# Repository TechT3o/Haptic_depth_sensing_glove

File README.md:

# Haptic_depth_sensing_glove

Haptic feedback glove device that uses a motor camera and mini motor disks to help visually impaired people understand the 3d space around them.

The idea is to mount a small camera on the palm of the visually impaired user, construct the depth map, and perform sensory substitution of vision by using a high-resolution haptic feedback glove comprised of an array of vibrational mini DC motor disks to assign a different intensity in the direction where the user's hand is pointing at, analogous to how close the object is.

The goal is for the user to be able to identify what type of object their hand is pointing at for object recognition and object fetching and for the user to be able to do wayfinding and navigate in a room using the device.

User studies that examine the usability (Learnability, Efficiency, Memorability, Errors, Satisfaction) and effectiveness of the device will be done.

# Hardware

- 1x [ESP32](https://www.espressif.com/en/products/socs/esp32)
- 1x [OV5640 camera module](https://www.amazon.com/Cameras-2592X1944-Industrial-Windows-Raspberry/dp/B088RD74VC?th=1)
- 20x [Mini motor disk](https://www.adafruit.com/product/1201#technical-details)
- 20x [p2n222A npn transistor](https://www.onsemi.com/pdf/datasheet/p2n2222a-d.pdf)
- 20x 30 Ohms resistor
- 20x 2.2k Ohms resistor
- 20x 33 pF capacitor
- 20x 1N4001 diode
- 20x [motor circuit PCB](https://github.com/TechT3o/Haptic_depth_sensing_glove/tree/main/PCB%20files)

## Motor driver circuit

The mini disk motors require around 100 mA of current in order to rotate at full speed with 5V power. The Arduino output pins can provide up to 10 mA, therefore we need a driver circuit to be able to power the motor using a PWM signal. The circuit shown in Figure 1 was built. It uses an NPN transistor whose base is connected to the GPIO output pin of the Arduino. When the PWM signal gets applied to the base of the transistor the Collector Emitter channel opens and current from the VCC flows through the disk motor and makes it spin with intensity analogous to the PWM signal. The resistor R2 limits the current flowing through the disk motor. A value of 30 Ohms was selected as 5V/30 = 166 mA max current that could flow through R2 ignoring rest of the circuit resistances. R1 was selected to limit the base current. As the base current is very small values of up to 5k could be selected but the chosen value for R1 in this project was 2.2k Ohms. The capacitor is used to soften voltage spikes from the power supply and suppress electrical noise from the motor's rotation and a diode is put to protect against back EMF.

*Figure 1: Motor driver circuit*

The PCB of this circuit shown in Figure 2 was made and the Gerber files were sent to [OSHPARK](https://oshpark.com/) for manufacturing.

*Figure 2: Motor driver PCB*

The received PCBs arrived and the components were soldered on top of it with the disk motors attached to the back of the PCB.

*Figure 3: PCB*

*Figure 4: Soldered circuits and motor coordinates*

## Camera

When choosing the camera we wanted a camera with a small size that could fit the device, as little distortion as possible (no wide angle cameras that tend to have a lot of barrel distortion), low latency and good enough resolution for the depth estimation model to give accurate results. The camera selected was a 5MP USB Camera Webcam with 60 Degree FOV and Autofocus Lens by IFWATER.

It used the OV5640 CMOS (Complementary Metal-Oxide-Semiconductor) image sensor which has high resolution of 2592 x 1944 pixels and can achieve frame rates of 30 FPS.

The location of the camera was another dilemma in our design consideration. As originally intended, it was supposed to be connected to the user's body. However, by relocating the camera to the palm, we eliminated the need to determine the depth relative to the hand, thereby simplifying the entire system. Placing the camera on the palm allows for a more natural interaction with the environment.

## Microcontroller
The microcontroller picked is an ESP32 DevkitC module. It was selected because it is affordable, has the options of wireless connectivity and low power consumption and unlike the Arduino Nano 33 BLE Sense which was the first attempt has no upper limit into how many GPIO pins can provide a PWM signal concurrently. 

*Figure 5: ESP32 module*

## Depth Estimation

In order to estimate the depth from a mono camera the vision transformer model DPT-Large by Intel was used. This transformer was trained on 1.4 million images for monocular depth estimation and it can predict the relative depth in an image frame. The Python class [MonoDepthEstimator](https://github.com/TechT3o/Haptic_depth_sensing_glove/blob/main/depth_estimation.py) implements this transformer with functions that can find the depth of a frame. For sanity checking the depth frames are visualized as a 3D point cloud using the [3D reconstruction](https://github.com/TechT3o/Haptic_depth_sensing_glove/blob/main/3d_reconstruct.py) script and the relative distances between the objects captured seem reasonable and is accurate for which object is closer to the camera. A sample depth video that is used to test the glove in its early stages and to visualize the depth estimation created by the [depth video creating script](https://github.com/TechT3o/Haptic_depth_sensing_glove/blob/main/depth_video_creating_script.py) is shown in Figure 5.

*Figure 6: Mono depth video example*

*Figure 7: Point cloud*

## Intensity mapping

The [IntensityMapper](https://github.com/TechT3o/Haptic_depth_sensing_glove/blob/main/intensity_mapper.py) class is responsible for getting the depth map and the positions of the motors on the glove and getting the PWM values by averaging the values around the corresponding pixel in the depth map. It performs the mapping by being input teh positions of the motors in a coordinate system on the frame of the device.

## Serial Communication

The [serial communicator](https://github.com/TechT3o/Haptic_depth_sensing_glove/blob/main/serial_com.py) class is responnsible for connecting the Python backend serially to the ESP32, transmitting the motor intensities and validating if those intensities were properly received.

## Microcontroller script

The [ESP32 script](https://github.com/TechT3o/Haptic_depth_sensing_glove/blob/main/motor_test.ino) is responsible for listening to the serial communication channel and reading and decoding the comma seperated string message that has the motor itnensities sent by the Python backend. Then it assigns these PWM intensities as PWM signals to the pins corresponding to each motor and send back the received intensities for the backend to confirm whether the communication was correct.

 ## Helper scripts

The [camera calibration](https://github.com/TechT3o/Haptic_depth_sensing_glove/blob/main/calibrate_cam_script.py) script is used to obtain camera parameters such as the foundational matrix, the intrinsic and extrinsic parameters and the lens distortions to be used in the 3D reconstruction or in estimating the depth.

## Prototype

A generic hand shaped frame was formed by gluing together wooden popsickles. Then all the electronics were mounted on top of the frame. The camera and the ESP32 are connected to the laptop through USB ports. The cables controlling the motors are connected to respective digital and analog pins (they both can provide PWM signals) of the ESP32. Lastly the power supply wires are connected to a 5V pwoer supply output and the ground of the power supply and the ESP32 are connected.

By running the [main.py](https://github.com/TechT3o/Haptic_depth_sensing_glove/blob/main/main.py) script we can operate the prototype and a visualziation that shows what the device captures and where the intensity of each motor is found from is shown.

*Figure 6: Prototype*

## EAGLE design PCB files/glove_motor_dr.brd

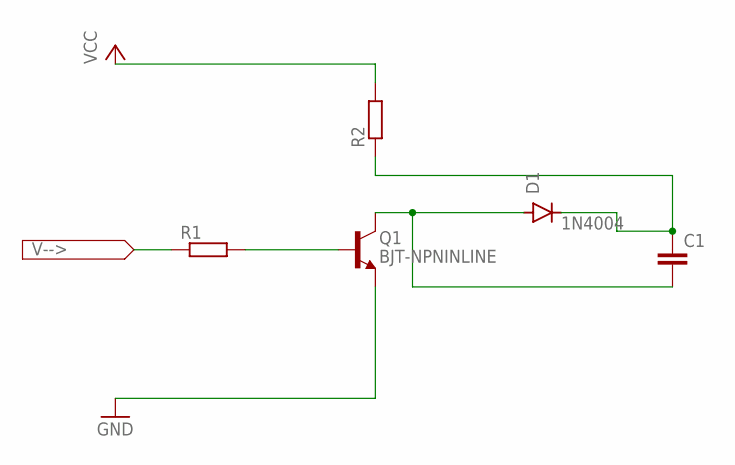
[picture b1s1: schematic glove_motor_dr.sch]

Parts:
C1: C-EU025-024X044; C025-024X044
D1: 1N4004; DO41-10
Q1: BJT-NPNINLINE; TO92I
R1, R2: R-EU_0207/7; 0207/7

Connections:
GND: Q1.E
MOTOR: C1.2, D1.A, Q1.C
unnamed: C1.1, D1.C, R2.1
unnamed: Q1.B, R1.2
VCC: R2.2

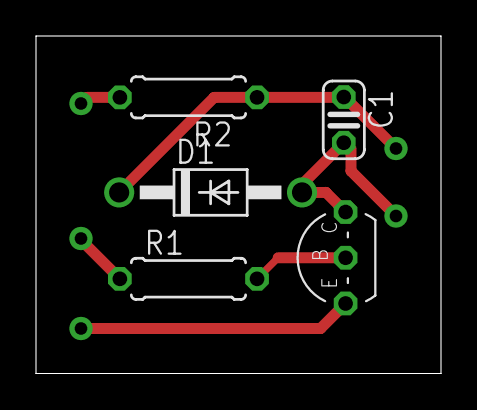
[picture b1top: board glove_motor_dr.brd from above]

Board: 2 copper layers, 22.5 x 18.8 mm, 5 parts (0 on the bottom side), 3 nets.

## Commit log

2023-10-16 Initial commit! Added depth_estimation.py a script that uses a depth transformer to find the depth of the images captured by laptops' camera Added calibrate_cam_script.py which can either use a folde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
2023-10-17 Refactored code
2023-11-07 added close camera to depth_estimation.py Created depth_video_creating_script.py Created intensity_mapper.py Created serial_com.py Created main.py
2023-11-07 Course deliverables
    Added course deliverable templates
2023-11-07 Update index.md
    Added basic information to index.md
2023-11-07 Update proposal.md
    Started completing proposal.md
2023-11-08 Update proposal.md
    Completed some more of proposal.md
2023-11-08 Update proposal.md
    Further updated proposal.md
2023-11-08 Update README.md
    Updated readme with hardware requirements and motor driver circuit details
2023-11-08 Update README.md
    Added text information for mono depth estimation
2023-11-08 Added Arduino code
2023-11-08 PCB files
    Added schematic, board file as well as the cam files used to manufacture the PCBs of the motor drivers
2023-11-08 Update README.md
    updated readme
2023-11-09 Update README.md
    further updated readme
2023-11-09 Update proposal.md
    Corrected some errors
2023-11-10 Update index.md
    updated index
2023-11-18 updated depth estimation, serial_com.py Added video_sensing_script.py to read depth video with glove Fixed mistakes in intensity_mapper.py and added drawing points and boxes Created main.py with main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
2023-12-11 Update report.md
    Added some parts of the report
2023-12-12 Update report.md
    Fixed images
    Updated evaluation and results
    Started writing abstract
    Added form in appendix 1
2023-12-13 Update report.md
    Added discussion section
2023-12-16 Update report.md
    Finished report
2023-12-16 Update index.md
    updated abstract and added final presentation link
2023-12-16 experimented with depth_estimation.py Finished main.py which is the file to be execute to operate the prototype
